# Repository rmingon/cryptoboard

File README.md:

# **Secure Private Messaging System Using STM32F103 and W5500**

In an era where digital privacy is constantly threatened, our project offers a truly secure and low-level encrypted messaging system. By utilizing the STM32F103 microcontroller, W5500 Ethernet module, and a simple HID keyboard, we create a direct, encrypted communication channel between identical devices.

## **Why is this system secure?**

### **1. Hardware-Level Encryption Initialization**  
Before using the system, each user must manually input an **interruption vector** for SHA-256 encryption using the connected keyboard. This vector serves as a unique key known only to the user and is not stored anywhere within the system, making external breaches virtually impossible.

### **2. No Third-Party Servers or Cloud Involvement**  
Unlike conventional messaging apps that rely on internet-based services, our system operates on a **direct peer-to-peer Ethernet connection**. This means no external servers can intercept or store messages.

### **3. Unique Session-Based Encryption**  
Each session requires the user to set up a unique **SHA-256 encryption vector**, ensuring that even if an attacker gains access to the system, previous messages cannot be decrypted.

### **4. Custom Communication Protocol**  
The messaging protocol is implemented at a very **low level**, avoiding standard protocols like TCP/IP that could be vulnerable to packet sniffing. This makes it extremely difficult for an attacker to analyze network traffic and extract meaningful data.

### **5. Limited Attack Surface**  
- The system is designed to be minimalistic, removing unnecessary software layers that could introduce vulnerabilities.  
- It does not rely on an OS or external APIs, reducing exposure to malware or exploits.  
- No wireless communication (e.g., Wi-Fi or Bluetooth), preventing remote attacks.

## **How It Works**

### **1. User Setup**
- Connect the HID keyboard.
- Input the custom **SHA-256 interruption vector** (not stored, only used in RAM).
- Configure the destination IP and port of the target device.

### **2. Sending a Message**
- The system encrypts the message using **SHA-256 hashing with the user-defined vector**.
- The encrypted message is sent via Ethernet using the W5500 module.

### **3. Receiving & Decryption**
- The recipient device receives the encrypted message.
- If the same interruption vector is manually entered, the message is decrypted successfully.
- If the incorrect vector is used, the message remains unreadable.

## **Why is it Impossible to Decrypt?**

- **No stored encryption keys:** Each session requires a manually entered vector, meaning even if a device is captured, past messages cannot be retrieved.  
- **Custom communication protocol:** Without knowing the exact system architecture, attackers cannot decipher the encryption method or data structure.  
- **SHA-256 strength:** Even with brute force, SHA-256 remains computationally infeasible to break.

## **Conclusion**

This project is perfect for individuals or organizations needing **absolute privacy** in communications. Whether for personal security, journalistic protection, or sensitive military applications, our STM32F103-based system ensures that messages remain confidential and beyond the reach of any third-party eavesdropping.

### Real

### 3d

### PCB

### Schematic

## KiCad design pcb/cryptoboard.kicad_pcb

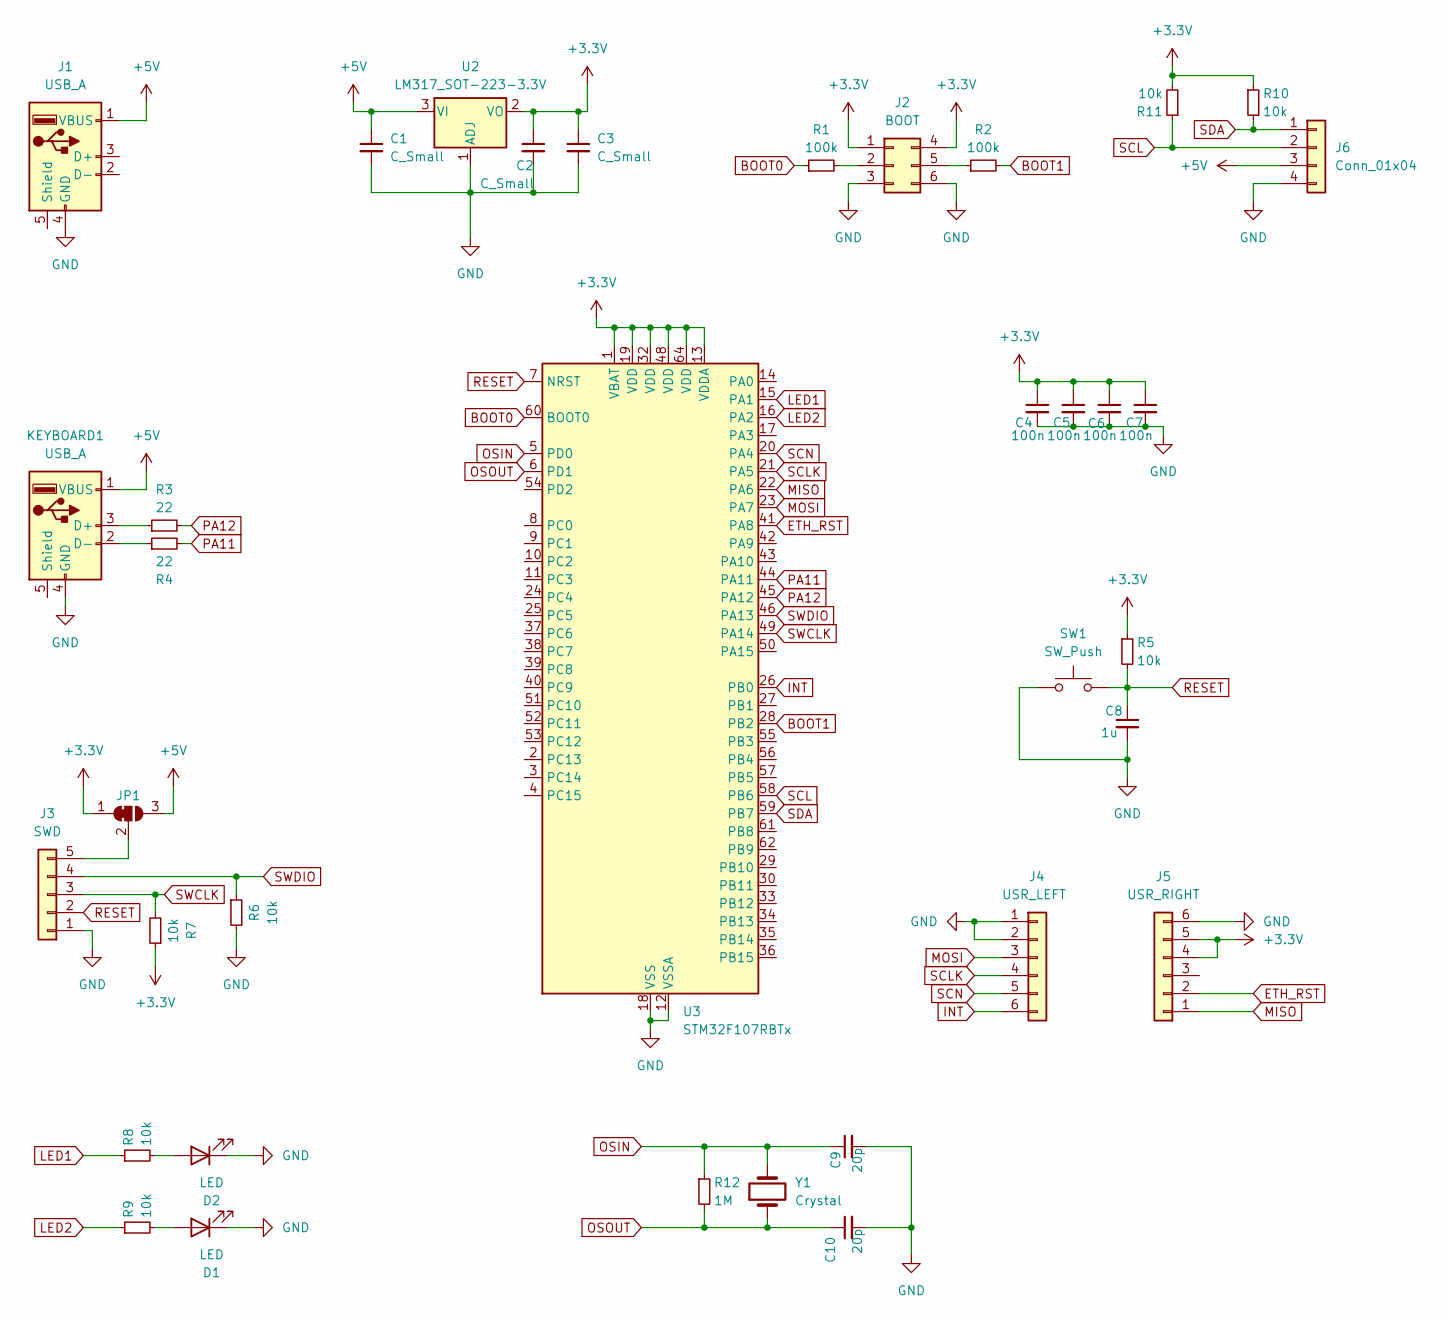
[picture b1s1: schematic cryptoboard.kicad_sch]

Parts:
C1, C2, C3: C_Small; C_0603_1608Metric
C4, C5, C6, C7: 100n; C_0603_1608Metric
C8: 1u; C_0603_1608Metric
C9, C10: 20p; C_0603_1608Metric
D1, D2: LED; D_0603_1608Metric
J1: USB_A; USB_Micro-B_Molex-105017-0001
J2: BOOT; PinHeader_2x03_P2.54mm_Vertical_new
J3: SWD; PinHeader_1x05_P2.54mm_Vertical
J4: USR_LEFT; PinHeader_1x06_P2.54mm_Vertical
J5: USR_RIGHT; PinHeader_1x06_P2.54mm_Vertical
J6: Conn_01x04; PinHeader_1x04_P2.54mm_Vertical
JP1: SolderJumper_3_Bridged12; SolderJumper-3_P1.3mm_Bridged12_RoundedPad1.0x1.5mm
KEYBOARD1: USB_A; USB_A_TE_292303-7_Horizontal
R1, R2: 100k; R_0603_1608Metric
R3, R4: 22; R_0603_1608Metric
R5, R6, R7, R8, R9, R10, R11: 10k; R_0603_1608Metric
R12: 1M; R_0603_1608Metric
SW1: SW_Push; SW_SPST_CK_RS282G05A3
U2: LM317_SOT-223-3.3V; SOT-223-3_TabPin2
U3: STM32F107RBTx; LQFP-64_10x10mm_P0.5mm
Y1: Crystal; Crystal_SMD_HC49-SD

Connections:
+3.3V: C2.1, C3.1, C4.1, C5.1, C6.1, C7.1, J2.1, J2.4, J5.4, J5.5, JP1.1 (A), R5.1, R7.1, R10.1, R11.2, U2.2 (VO), U3.1 (VBAT), U3.13 (VDDA), U3.19 (VDD), U3.32 (VDD), U3.48 (VDD), U3.64 (VDD)
+5V: C1.1, J1.1 (VBUS), J6.3, JP1.3 (B), KEYBOARD1.1 (VBUS), U2.3 (VI)
BOOT0: R1.1, U3.60 (BOOT0)
BOOT1: R2.2, U3.28 (PB2)
ETH_RST: J5.2, U3.41 (PA8)
GND: C1.2, C2.2, C3.2, C4.2, C5.2, C6.2, C7.2, C8.2, C9.2, C10.2, D1.1 (K), D2.1 (K), J1.4 (GND), J2.3, J2.6, J3.1, J4.1, J4.2, J5.6, J6.4, KEYBOARD1.4 (GND), R6.2, SW1.1, U2.1 (ADJ), U3.12 (VSSA), U3.18 (VSS), U3.31 (VSS), U3.47 (VSS), U3.63 (VSS)
INT: J4.6, U3.26 (PB0)
LED1: R8.1, U3.15 (PA1)
LED2: R9.1, U3.16 (PA2)
MISO: J5.1, U3.22 (PA6)
MOSI: J4.3, U3.23 (PA7)
unnamed: D1.2 (A), R9.2
unnamed: D2.2 (A), R8.2
unnamed: J2.2, R1.2
unnamed: J2.5, R2.1
unnamed: J3.5, JP1.2 (C)
unnamed: KEYBOARD1.3 (D+), R3.1
unnamed: KEYBOARD1.2 (D-), R4.1
OSIN: C9.1, R12.1, U3.5 (PD0), Y1.2
OSOUT: C10.1, R12.2, U3.6 (PD1), Y1.1
PA11: R4.2, U3.44 (PA11)
PA12: R3.2, U3.45 (PA12)
RESET: C8.1, J3.2, R5.2, SW1.2, U3.7 (NRST)
SCL: J6.2, R11.1, U3.58 (PB6)
SCLK: J4.4, U3.21 (PA5)
SCN: J4.5, U3.20 (PA4)
SDA: J6.1, R10.2, U3.59 (PB7)
SWCLK: J3.3, R7.2, U3.49 (PA14)
SWDIO: J3.4, R6.1, U3.46 (PA13)

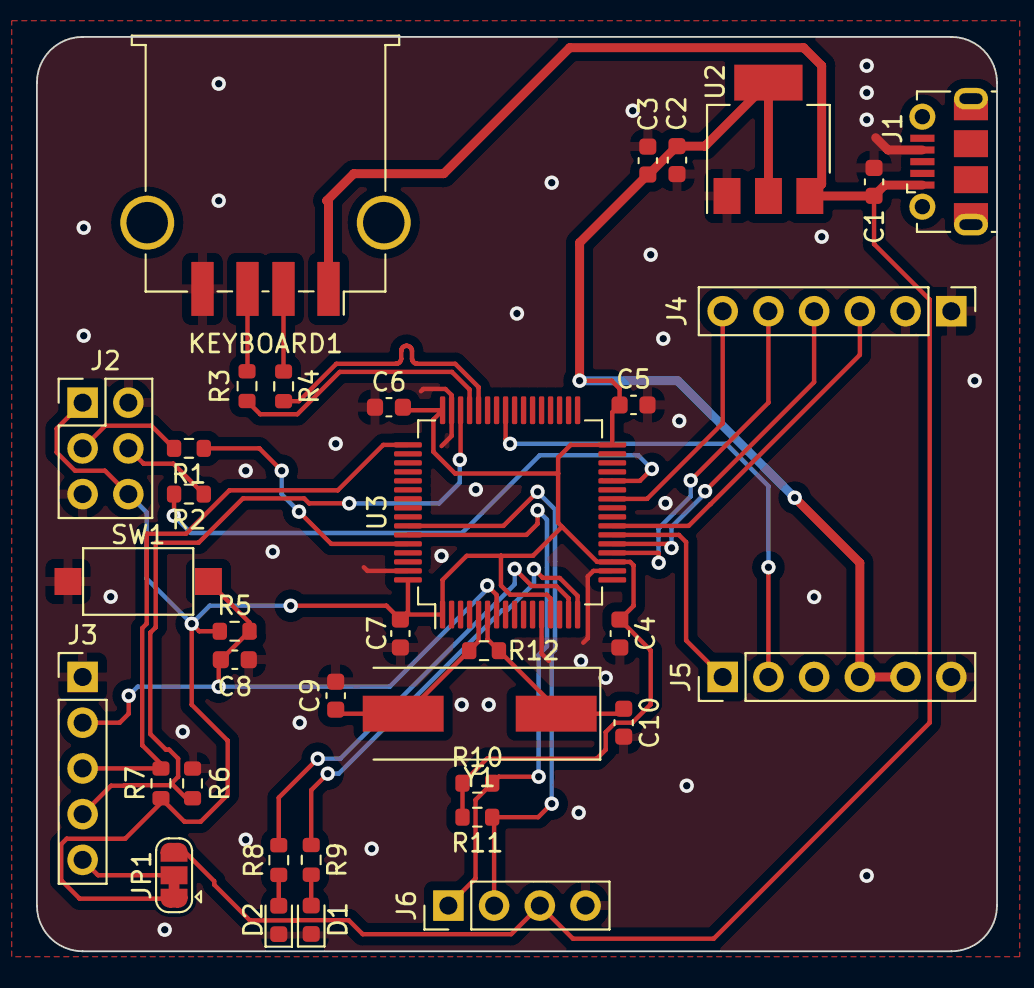
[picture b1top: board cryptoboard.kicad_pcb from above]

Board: 2 copper layers, 53.3 x 50.8 mm, 36 parts (0 on the bottom side), 29 nets.

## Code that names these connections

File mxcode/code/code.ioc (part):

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Mcu.Name=STM32F107R(B-C)Tx
Mcu.Package=LQFP64
Mcu.UserName=STM32F107RBTx
PA1.GPIOParameters=PinState
PA1.PinState=GPIO_PIN_SET
PA1.Signal=GPIO_Output
PA11.Mode=Host_Only
PA11.Signal=USB_OTG_FS_DM
PA12.Mode=Host_Only
PA12.Signal=USB_OTG_FS_DP
PA5.Mode=Full_Duplex_Master
PA5.Signal=SPI1_SCK
PA6.Mode=Full_Duplex_Master
PA6.Signal=SPI1_MISO
PA7.Mode=Full_Duplex_Master
PA7.Signal=SPI1_MOSI
PB6.Mode=I2C
PB6.Signal=I2C1_SCL
PB7.Mode=I2C
PB7.Signal=I2C1_SDA
PD0-OSC_IN.Mode=HSE-External-Oscillator
PD0-OSC_IN.Signal=RCC_OSC_IN
PD1-OSC_OUT.Mode=HSE-External-Oscillator
PD1-OSC_OUT.Signal=RCC_OSC_OUT
RCC.SYSCLKFreq_VALUE=72000000
RCC.SYSCLKSource=RCC_SYSCLKSOURCE_PLLCLK
board=custom

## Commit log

2024-05-18 add resistor
2024-05-19 add boot connector
2024-05-19 add DC DC
2024-05-19 UPDATE shcema
2024-05-19 add stm32 capacitor
2024-05-20 add swd
2024-05-20 add vcc
2024-05-20 add usr es1
2024-05-20 add i2c + usr
2024-05-20 add pcb
2024-05-20 add wiring
2024-05-20 fill ground
2024-05-21 add crystal
2024-05-21 add crystal psb
2024-05-21 add drc
2024-06-04 stm32f103 to stm32f107
2024-06-19 update project
2024-06-19 add new code project
2024-06-20 keyboard code
2024-06-21 add spi and I2c
2024-06-21 update wiring
2024-06-21 update from cudeIDE
2024-06-21 edit output directory
2024-07-07 add screen code
2025-03-02 add pictures
